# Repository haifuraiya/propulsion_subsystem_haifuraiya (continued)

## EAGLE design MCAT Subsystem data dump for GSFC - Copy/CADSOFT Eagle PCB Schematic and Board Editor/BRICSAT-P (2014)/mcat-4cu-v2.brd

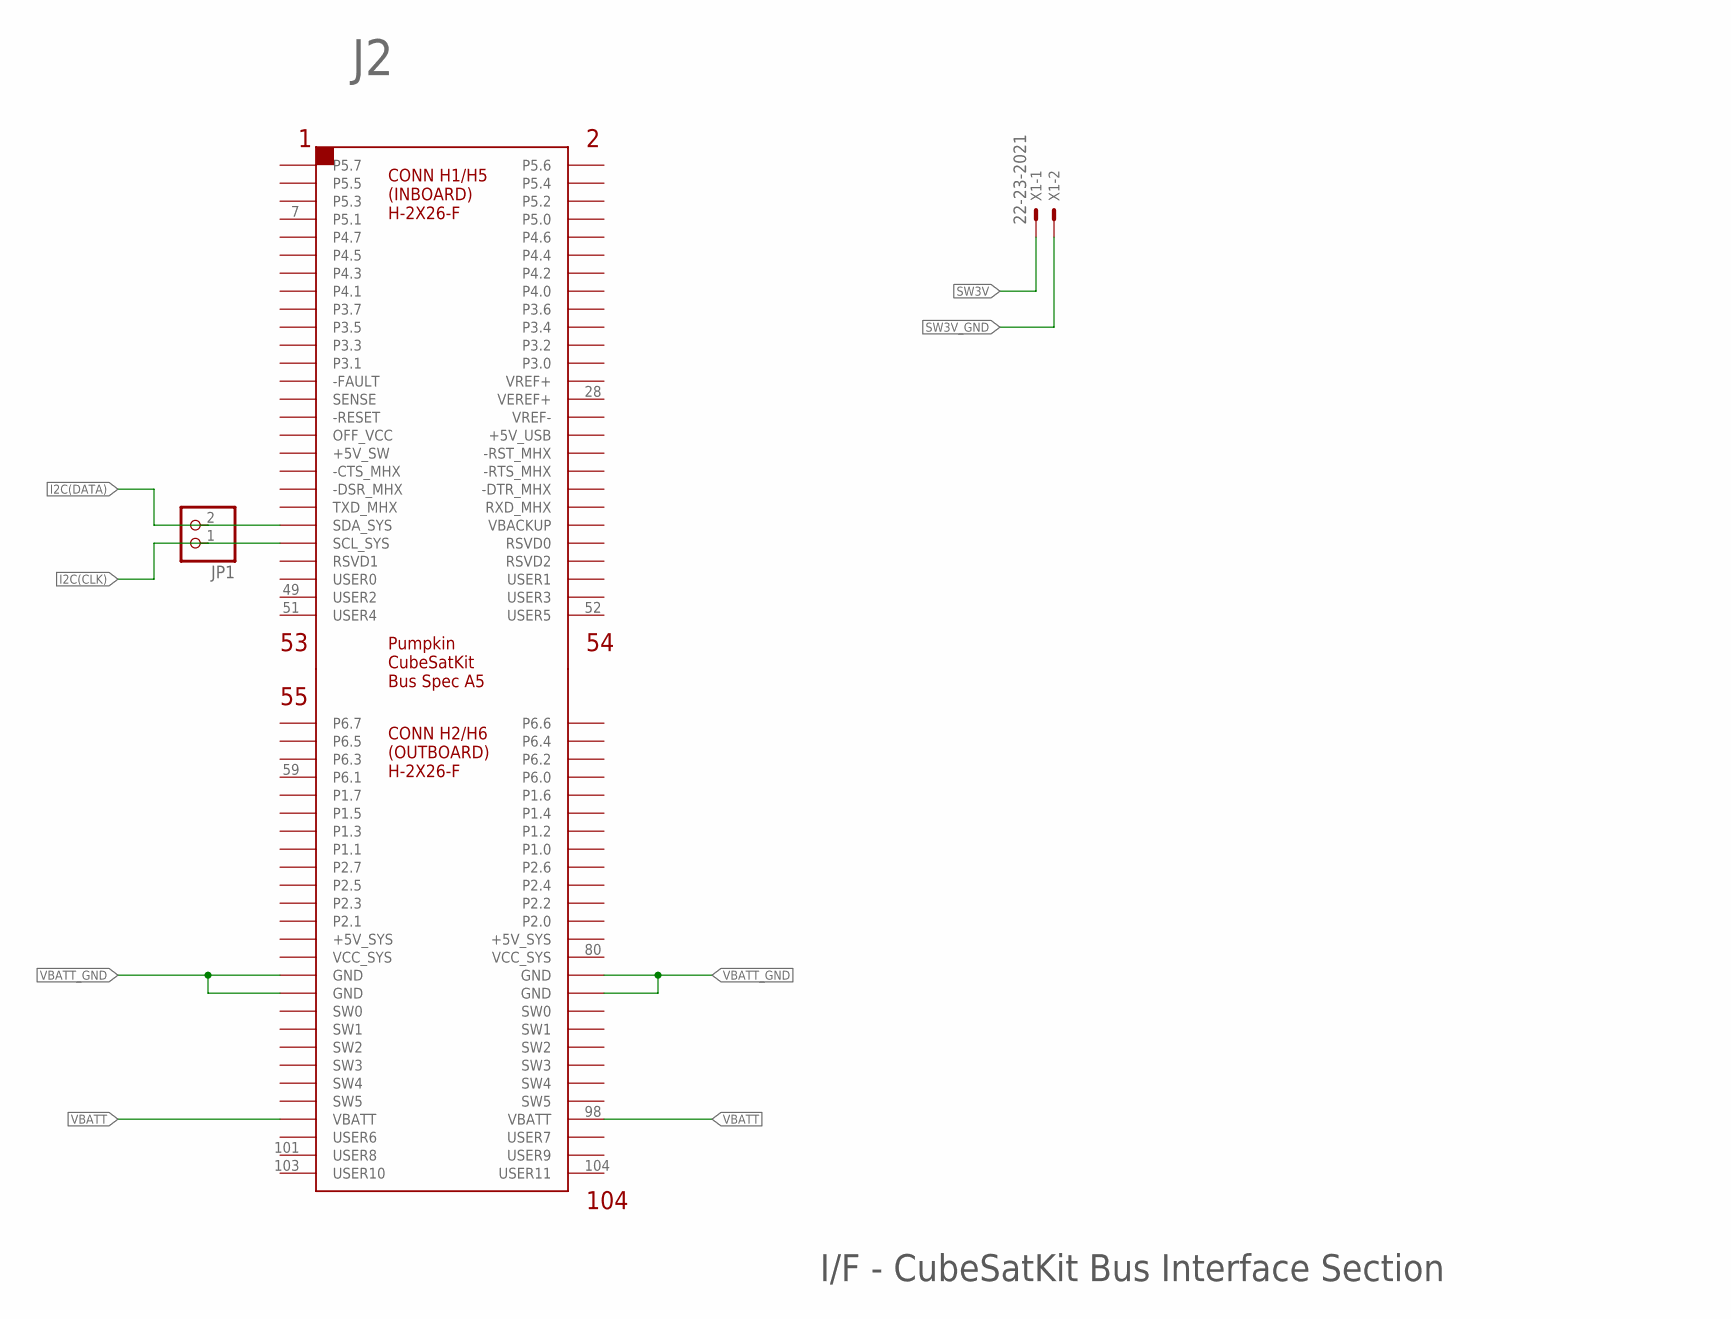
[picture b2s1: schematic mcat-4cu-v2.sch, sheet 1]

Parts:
J2: CSK-BUS-CONN2X2X26; CSK-BUS-PKG
JP1: PINHD-1X2; 1X02
X1: 22-23-2021

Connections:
I2C(CLK): J2.43 (SCL_SYS), JP1.1; also elsewhere on the board
I2C(DATA): J2.41 (SDA_SYS), JP1.2; also elsewhere on the board
unnamed: J2.82 (GND), J2.84 (GND)
SW3V: X1.1; also elsewhere on the board
SW3V_GND: X1.2; also elsewhere on the board
VBATT: J2.97 (VBATT), J2.98 (VBATT); also elsewhere on the board
VBATT_GND: J2.81 (GND), J2.83 (GND); also elsewhere on the board

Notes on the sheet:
I/F - CubeSatKit Bus Interface Section

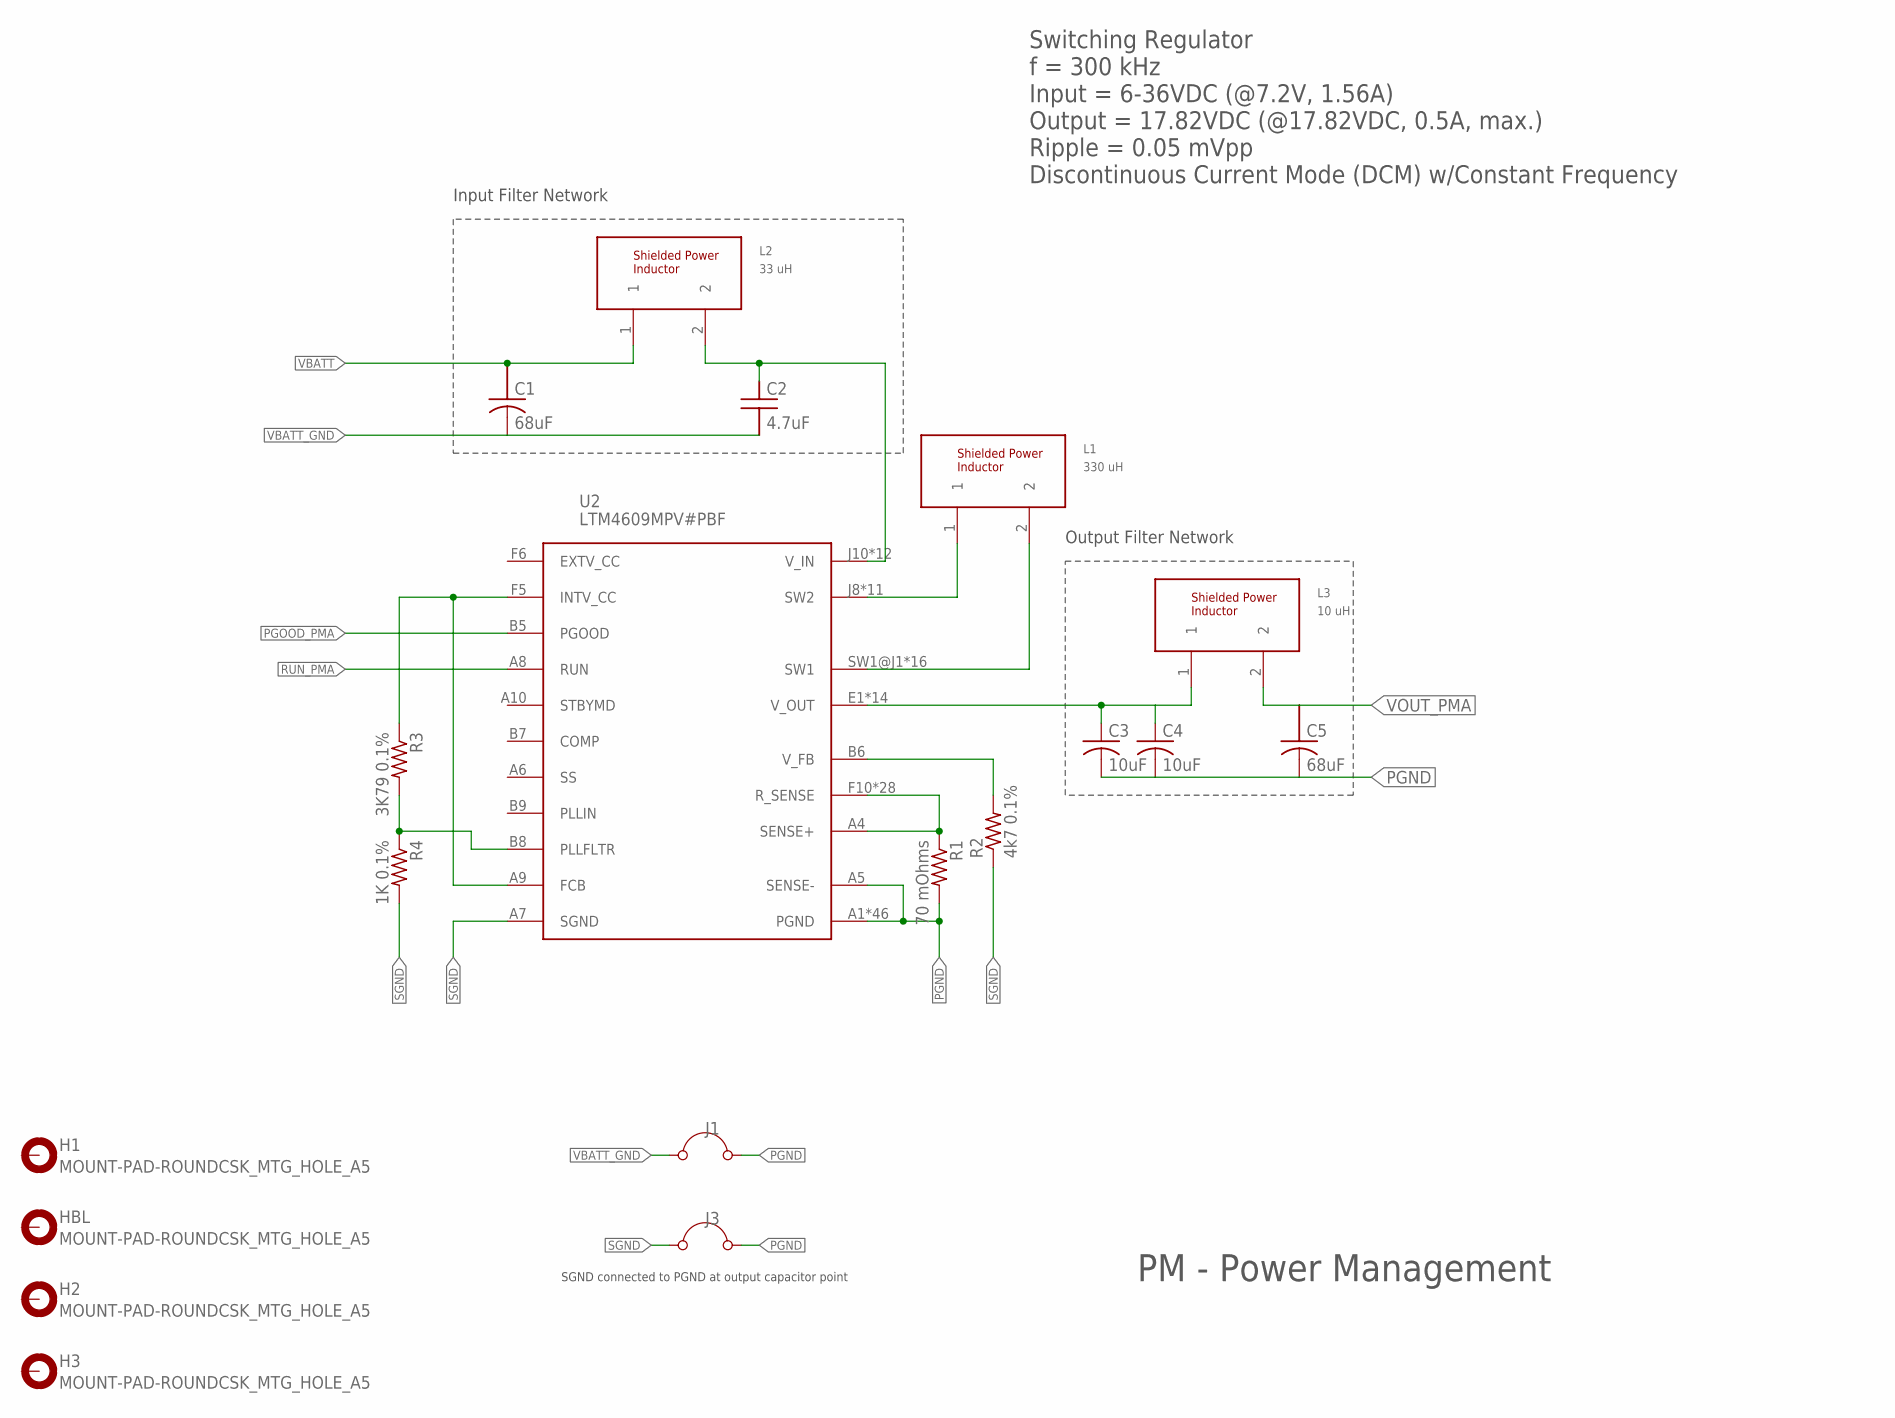
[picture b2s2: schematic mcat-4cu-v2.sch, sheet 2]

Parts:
C1, C5: 68uF; OS-CON-SVPF-F12
C2: 4.7uF; MLCC-X7R-1210
C3, C4: 10uF; C1210K
H1, H2, H3: MOUNT-PAD-ROUNDCSK_MTG_HOLE_A5; CSK_MOUNTING_HOLE
HBL: MOUNT-PAD-ROUNDCSK_MTG_HOLE_A5; CSK_MOUNTING_HOLE
J1, J3: JUMPER; 05
L1: 330 uH; MSS1048
L2: 33 uH; MSS1048
L3: 10 uH; SERIES-POWER-INDUCTORS
R1: 70 mOhms; R1206
R2: 4k7 0.1%; R0603
R3: 3K79 0.1%; R0805
R4: 1K 0.1%; R0805
U2: LTM4609MPV#PBF; LGA-141-LTC-05-08-1840-B

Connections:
INTVCC_OUT: R3.1, U2.A9 (FCB), U2.F5 (INTV_CC)
unnamed: R1.1, U2.A4 (SENSE+), U2.F10 (R_SENSE), U2.F11 (R_SENSE), U2.F12 (R_SENSE), U2.G5 (R_SENSE), U2.G6 (R_SENSE), U2.G7 (R_SENSE), U2.G8 (R_SENSE), U2.G9 (R_SENSE), U2.G10 (R_SENSE), U2.G11 (R_SENSE), U2.G12 (R_SENSE), U2.H5 (R_SENSE), U2.H6 (R_SENSE), U2.H7 (R_SENSE), U2.H8 (R_SENSE), U2.H9 (R_SENSE), U2.H10 (R_SENSE), U2.H11 (R_SENSE), U2.H12 (R_SENSE), U2.J5 (R_SENSE), U2.J6 (R_SENSE), U2.J7 (R_SENSE), U2.K5 (R_SENSE), U2.K6 (R_SENSE), U2.L5 (R_SENSE), U2.L6 (R_SENSE), U2.M5 (R_SENSE), U2.M6 (R_SENSE)
unnamed: R2.2, U2.B6 (V_FB)
PGND: C3.2, C4.2, C5.K1 (K), J1.2 (-), J3.2 (-), R1.2, U2.A1 (PGND), U2.A2 (PGND), U2.A3 (PGND), U2.A5 (SENSE-), U2.A11 (PGND), U2.A12 (PGND), U2.B1 (PGND), U2.B2 (PGND), U2.B3 (PGND), U2.B4 (PGND), U2.B10 (PGND), U2.B11 (PGND), U2.B12 (PGND), U2.C1 (PGND), U2.C2 (PGND), U2.C3 (PGND), U2.C4 (PGND), U2.C5 (PGND), U2.C6 (PGND), U2.C7 (PGND), U2.C8 (PGND), U2.C9 (PGND), U2.C10 (PGND), U2.C11 (PGND), U2.C12 (PGND), U2.D1 (PGND), U2.D2 (PGND), U2.D3 (PGND), U2.D4 (PGND), U2.D5 (PGND), U2.D6 (PGND), U2.D7 (PGND), U2.D8 (PGND), U2.D9 (PGND), U2.D10 (PGND), U2.D11 (PGND), U2.D12 (PGND), U2.E3 (PGND), U2.E4 (PGND), U2.E5 (PGND), U2.E6 (PGND), U2.E7 (PGND), U2.E8 (PGND), U2.E9 (PGND), U2.E10 (PGND), U2.E11 (PGND), U2.E12 (PGND)
PGOOD_PMA: U2.B5 (PGOOD)
RUN_PMA: U2.A8 (RUN)
SETFREQ: R3.2, R4.1, U2.B8 (PLLFLTR)
SGND: J3.1 (+), R2.1, R4.2, U2.A7 (SGND); also elsewhere on the board
SW1: L1.2, U2.SW1@J1 (SW1), U2.SW1@J2 (SW1), U2.SW1@J3 (SW1), U2.SW1@J4 (SW1), U2.SW1@K1 (SW1), U2.SW1@K2 (SW1), U2.SW1@K3 (SW1), U2.SW1@K4 (SW1), U2.SW1@L1 (SW1), U2.SW1@L2 (SW1), U2.SW1@L3 (SW1), U2.SW1@L4 (SW1), U2.SW1@M1 (SW1), U2.SW1@M2 (SW1), U2.SW1@M3 (SW1), U2.SW1@M4 (SW1)
SW2: L1.1, U2.J8 (SW2), U2.J9 (SW2), U2.K7 (SW2), U2.K8 (SW2), U2.K9 (SW2), U2.L7 (SW2), U2.L8 (SW2), U2.L9 (SW2), U2.M7 (SW2), U2.M8 (SW2), U2.M9 (SW2)
VBATT: C1.A1 (A), L2.1; also elsewhere on the board
VBATT_GND: C1.K1 (K), C2.2, J1.1 (+); also elsewhere on the board
VIN_PMA: C2.1, L2.2, U2.J10 (V_IN), U2.J11 (V_IN), U2.J12 (V_IN), U2.K10 (V_IN), U2.K11 (V_IN), U2.K12 (V_IN), U2.L10 (V_IN), U2.L11 (V_IN), U2.L12 (V_IN), U2.M10 (V_IN), U2.M11 (V_IN), U2.M12 (V_IN)
VOUTA: C3.1, C4.1, L3.1, U2.E1 (V_OUT), U2.E2 (V_OUT), U2.F1 (V_OUT), U2.F2 (V_OUT), U2.F3 (V_OUT), U2.F4 (V_OUT), U2.G1 (V_OUT), U2.G2 (V_OUT), U2.G3 (V_OUT), U2.G4 (V_OUT), U2.H2 (V_OUT), U2.H3 (V_OUT), U2.H4 (V_OUT), U2.VOUT (V_OUT)
VOUT_PMA: C5.A1 (A), L3.2

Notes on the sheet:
PM - Power Management
Input Filter Network
SGND connected to PGND at output capacitor point
Output Filter Network
Switching Regulator f = 300 kHz Input = 6-36VDC (@7.2V, 1.56A) Output = 17.82VDC (@17.82VDC, 0.5A, max.) Ripple = 0.05 mVpp Discontinuous Current Mode (DCM) w/Constant Frequency

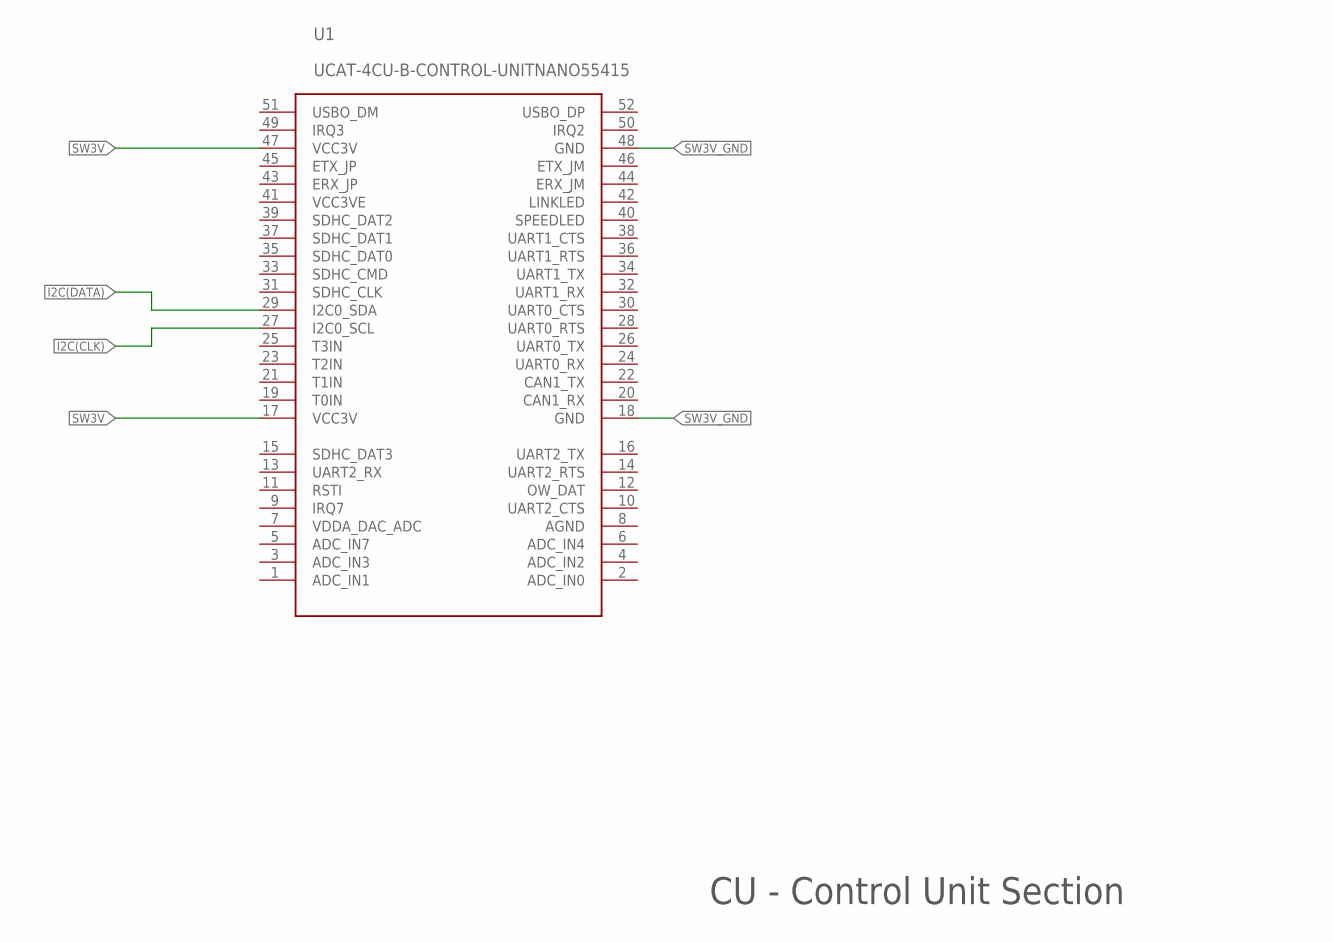
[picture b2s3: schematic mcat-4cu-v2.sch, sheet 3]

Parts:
U1: UCAT-4CU-B-CONTROL-UNITNANO55415; MOLEX-MINI-PCI-EXPRESS-8MM-52CKT

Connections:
I2C(CLK): U1.27 (I2C0_SCL); also elsewhere on the board
I2C(DATA): U1.29 (I2C0_SDA); also elsewhere on the board
SW3V: U1.17 (VCC3V), U1.47 (VCC3V); also elsewhere on the board
SW3V_GND: U1.48 (GND); also elsewhere on the board

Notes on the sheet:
CU - Control Unit Section

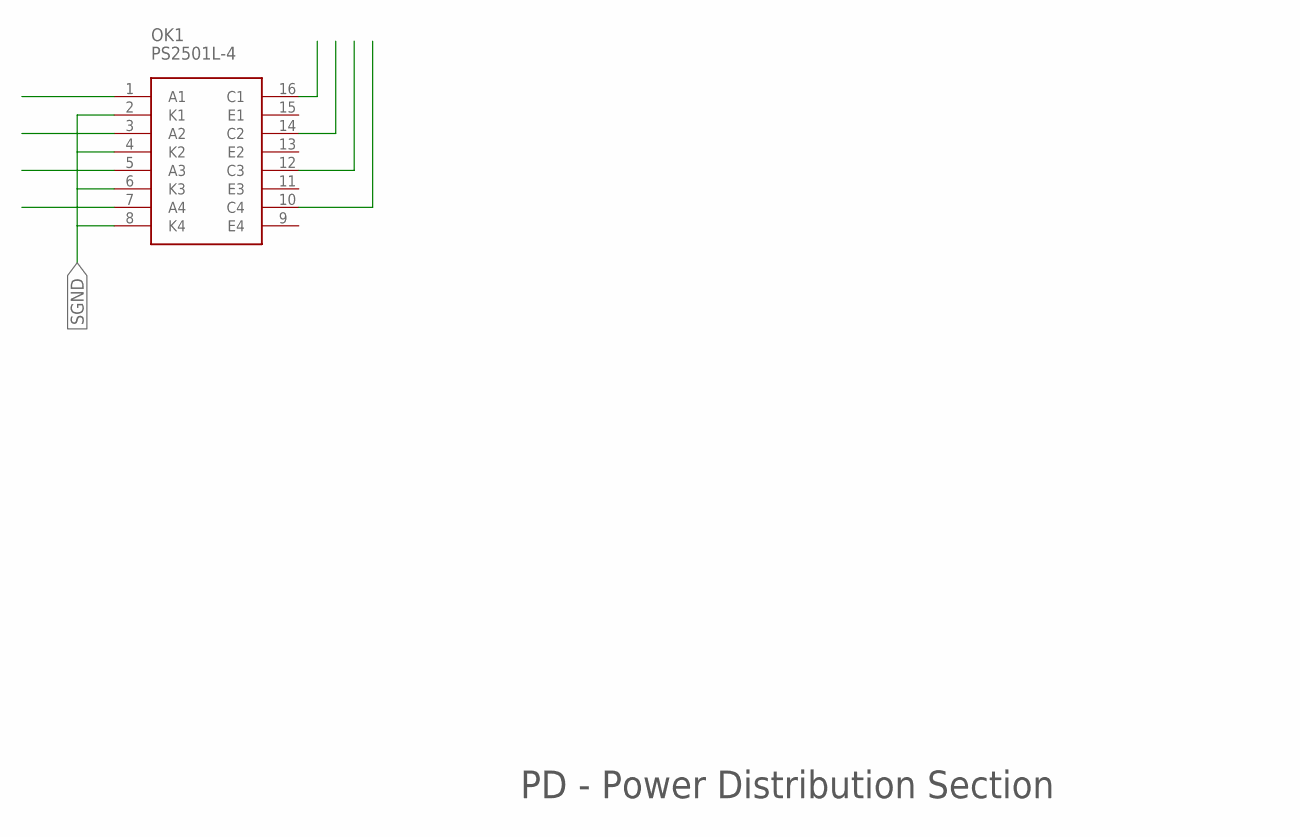
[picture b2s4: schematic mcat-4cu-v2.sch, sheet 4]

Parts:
OK1: PS2501L-4

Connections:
SGND: OK1.2 (K1), OK1.4 (K2), OK1.6 (K3), OK1.8 (K4); also elsewhere on the board

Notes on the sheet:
PD - Power Distribution Section

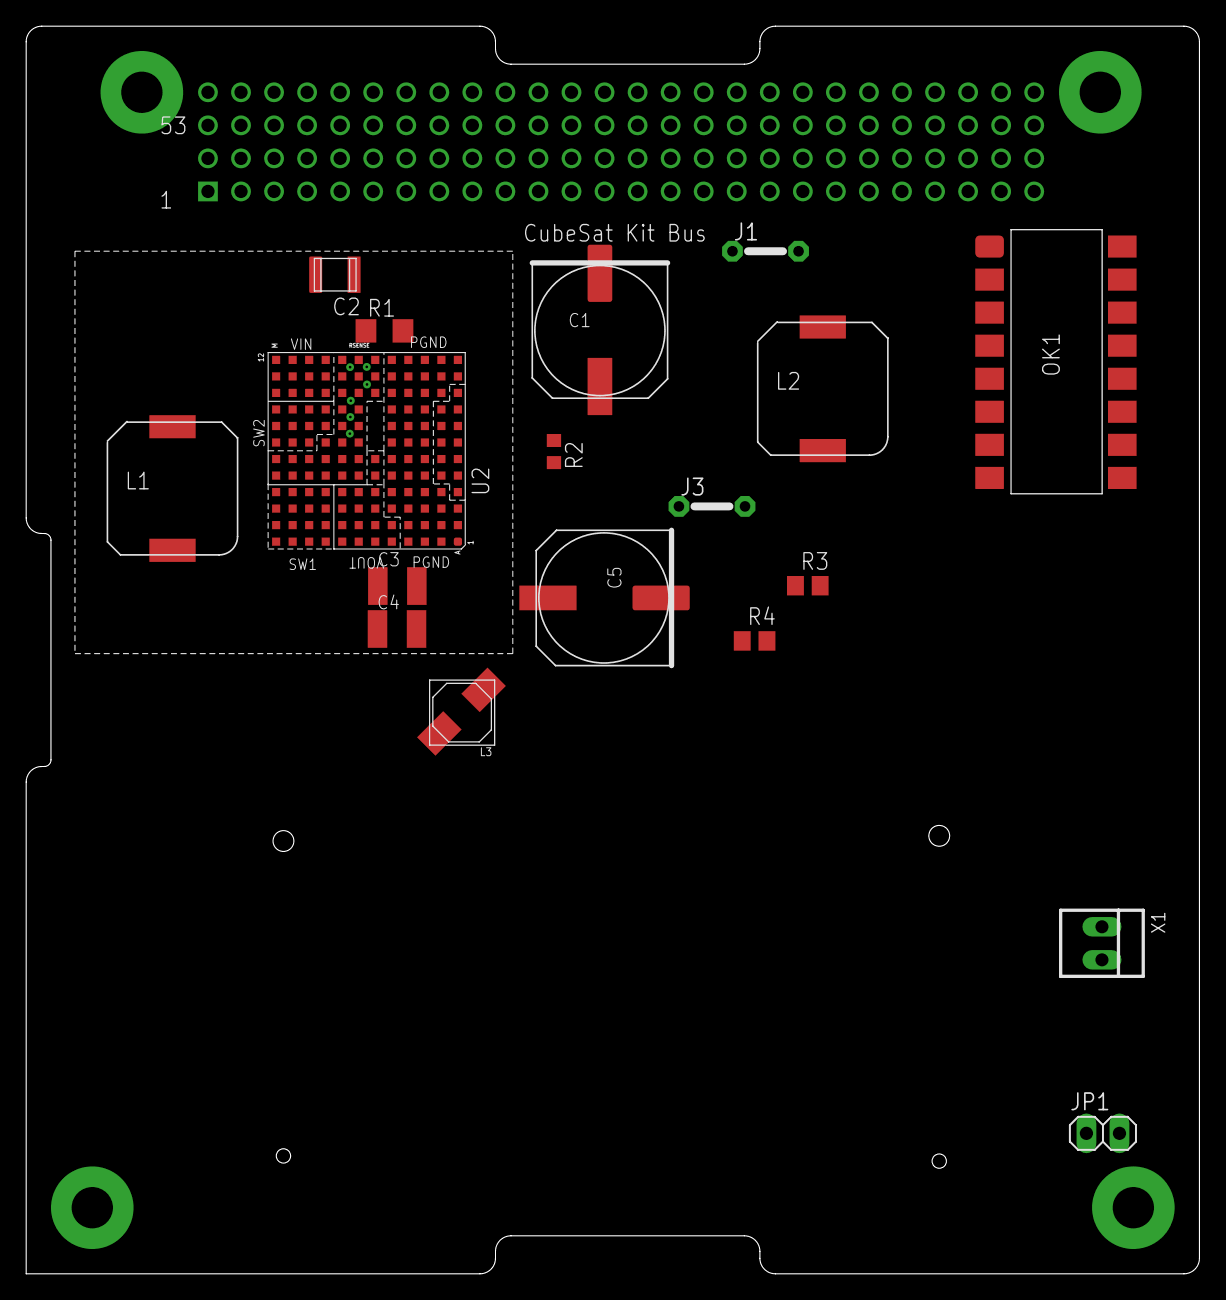
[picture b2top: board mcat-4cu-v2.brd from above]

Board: 4 copper layers, 90.2 x 95.9 mm, 24 parts (1 on the bottom side), 18 nets.

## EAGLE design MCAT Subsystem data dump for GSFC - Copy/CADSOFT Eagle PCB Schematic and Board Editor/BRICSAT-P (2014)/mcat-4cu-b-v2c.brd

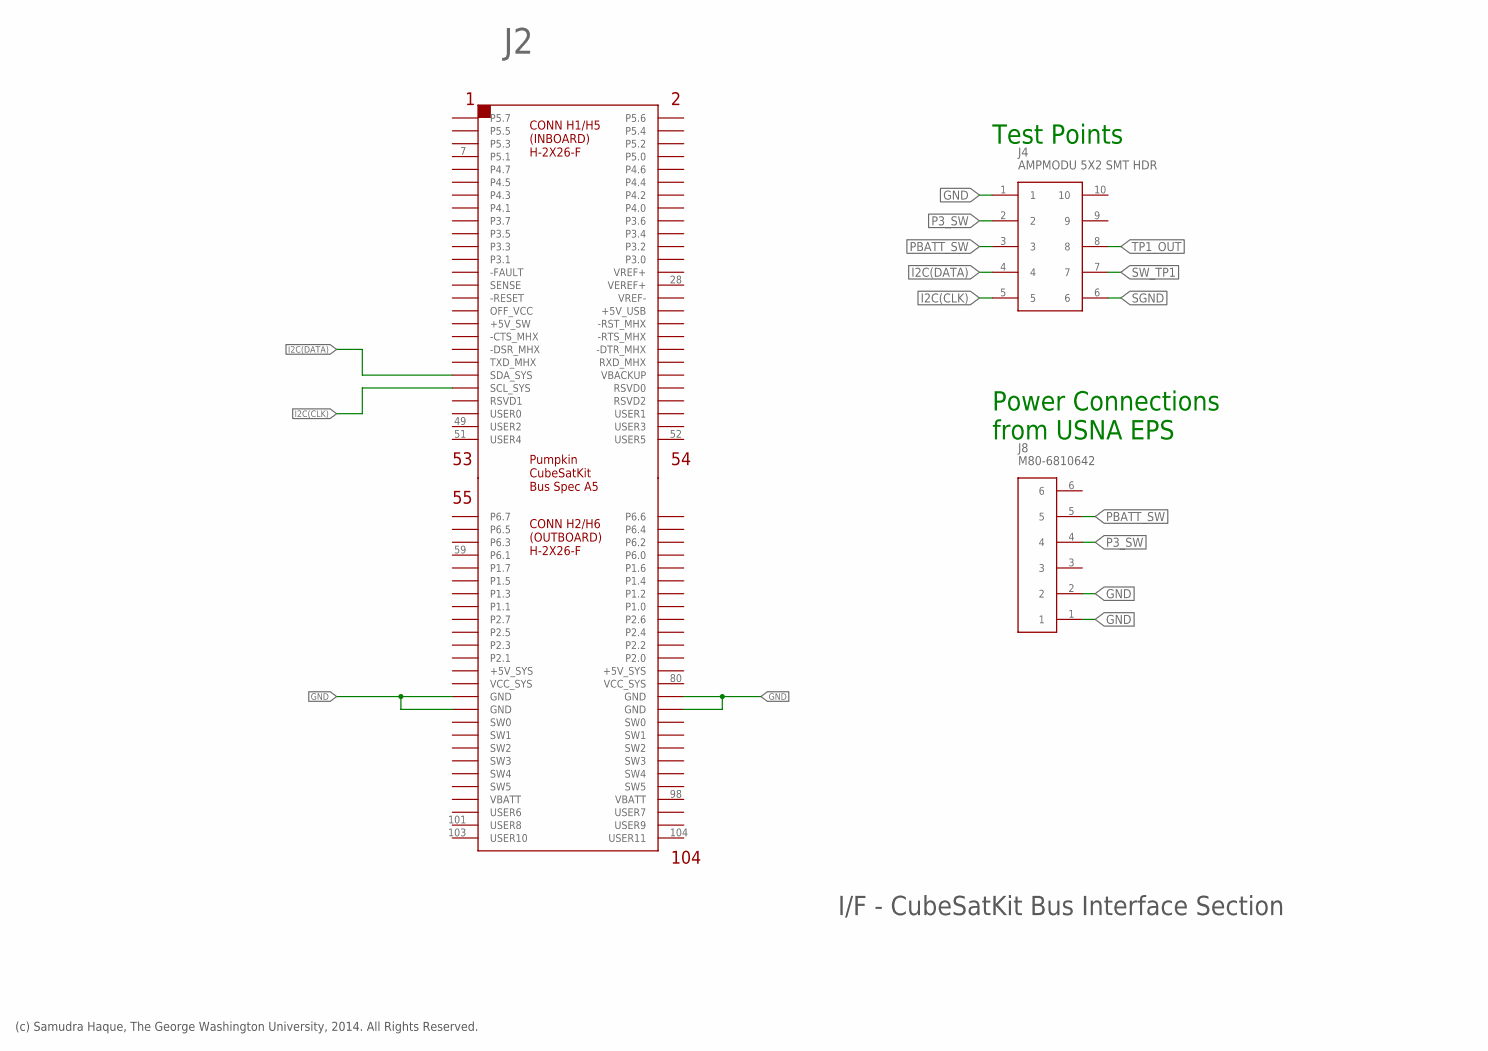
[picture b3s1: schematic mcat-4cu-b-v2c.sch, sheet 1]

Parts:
J2: CSK-BUS-CONN2X2X26; CSK-BUS-PKG
J4: AMPMODU 5X2 SMT HDR; AMPMODU-SMT-PIN-HEADER-5X2
J8: M80-6810642; M80-68106

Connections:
GND: J2.81 (GND), J2.82 (GND), J2.83 (GND), J2.84 (GND), J4.1, J8.1, J8.2; also elsewhere on the board
I2C(CLK): J2.43 (SCL_SYS), J4.5; also elsewhere on the board
I2C(DATA): J2.41 (SDA_SYS), J4.4; also elsewhere on the board
P3_SW: J4.2, J8.4; also elsewhere on the board
PBATT_SW: J4.3, J8.5; also elsewhere on the board
SGND: J4.6; also elsewhere on the board
SW_TP1: J4.7; also elsewhere on the board
TP1_OUT: J4.8; also elsewhere on the board

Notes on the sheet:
I/F - CubeSatKit Bus Interface Section
Test Points
(c) Samudra Haque, The George Washington University, 2014. All Rights Reserved.
Power Connections from USNA EPS

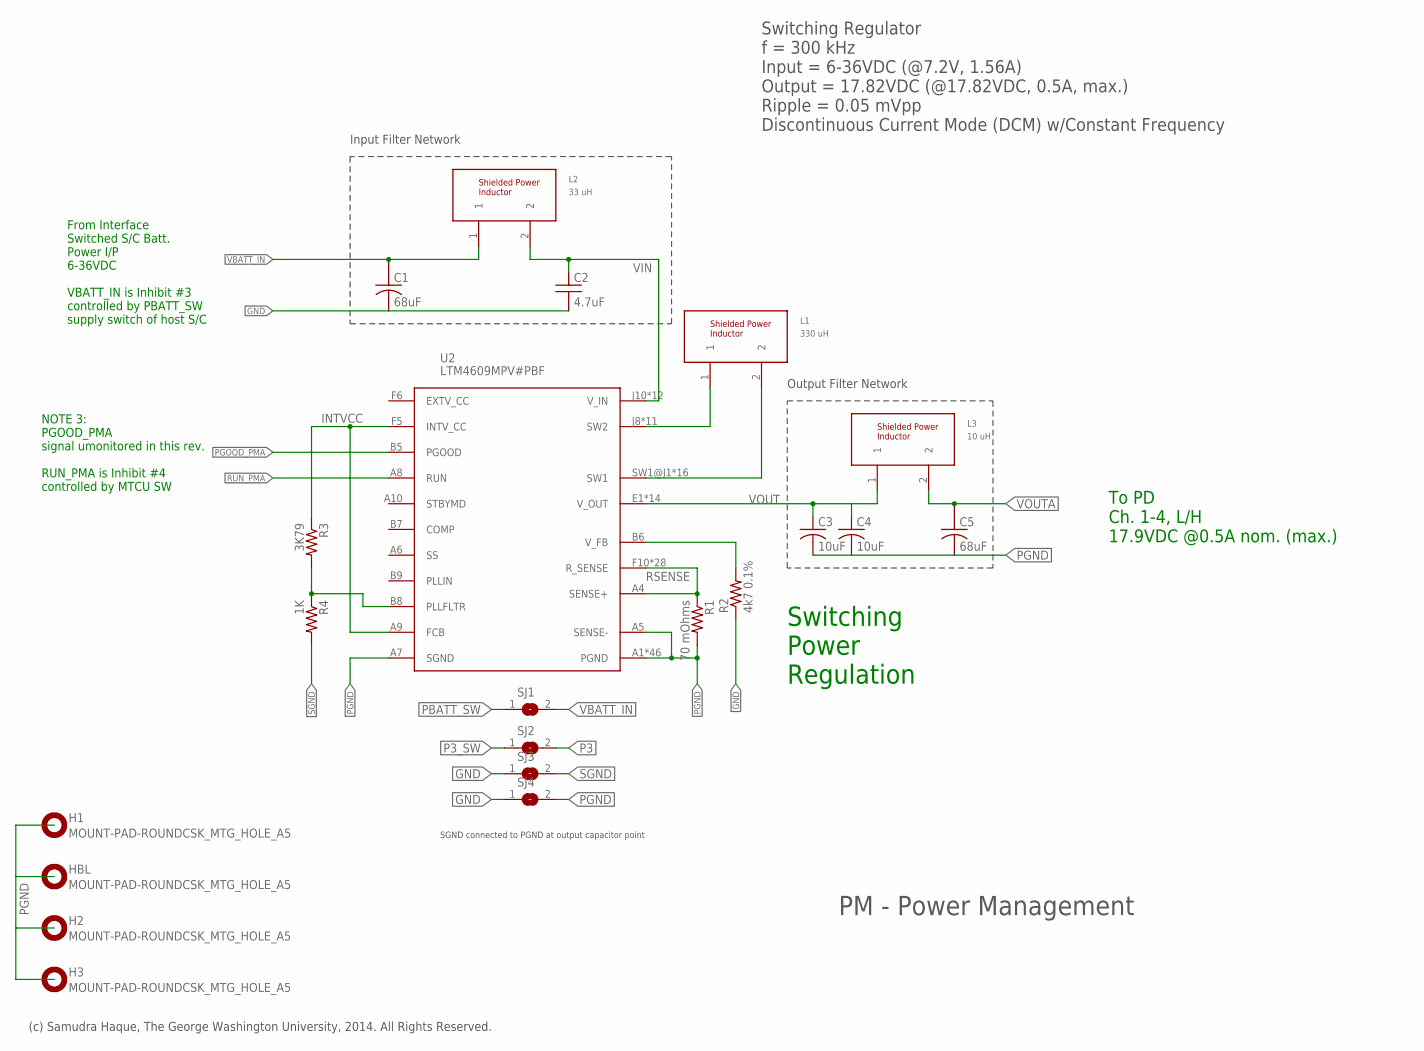
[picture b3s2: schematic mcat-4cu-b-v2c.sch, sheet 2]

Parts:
C1, C5: 68uF; OS-CON-SVPF-F12
C2: 4.7uF; MLCC-X7R-1210
C3, C4: 10uF; C1210K
H1, H2, H3: MOUNT-PAD-ROUNDCSK_MTG_HOLE_A5; CSK_MOUNTING_HOLE
HBL: MOUNT-PAD-ROUNDCSK_MTG_HOLE_A5; CSK_MOUNTING_HOLE
L1: 330 uH; MSS1048
L2: 33 uH; MSS1048
L3: 10 uH; SERIES-POWER-INDUCTORS
R1: 70 mOhms; R1206
R2: 4k7 0.1%; R0603
R3: 3K79; R0805
R4: 1K; R0805
SJ1, SJ2, SJ3, SJ4: SJ
U2: LTM4609MPV#PBF; LGA-141-LTC-05-08-1840-B

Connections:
GND: C1.K1 (K), C2.2, R2.1, SJ3.1, SJ4.1; also elsewhere on the board
INTVCC: R3.1, U2.A9 (FCB), U2.F5 (INTV_CC); also elsewhere on the board
unnamed: R2.2, U2.B6 (V_FB)
P3: SJ2.2; also elsewhere on the board
P3_SW: SJ2.1; also elsewhere on the board
PBATT_SW: SJ1.1; also elsewhere on the board
PGND: C3.2, C4.2, C5.K1 (K), H1.P$1, H2.P$1, H3.P$1, HBL.P$1, R1.2, SJ4.2, U2.A1 (PGND), U2.A2 (PGND), U2.A3 (PGND), U2.A5 (SENSE-), U2.A7 (SGND), U2.A11 (PGND), U2.A12 (PGND), U2.B1 (PGND), U2.B2 (PGND), U2.B3 (PGND), U2.B4 (PGND), U2.B10 (PGND), U2.B11 (PGND), U2.B12 (PGND), U2.C1 (PGND), U2.C2 (PGND), U2.C3 (PGND), U2.C4 (PGND), U2.C5 (PGND), U2.C6 (PGND), U2.C7 (PGND), U2.C8 (PGND), U2.C9 (PGND), U2.C10 (PGND), U2.C11 (PGND), U2.C12 (PGND), U2.D1 (PGND), U2.D2 (PGND), U2.D3 (PGND), U2.D4 (PGND), U2.D5 (PGND), U2.D6 (PGND), U2.D7 (PGND), U2.D8 (PGND), U2.D9 (PGND), U2.D10 (PGND), U2.D11 (PGND), U2.D12 (PGND), U2.E3 (PGND), U2.E4 (PGND), U2.E5 (PGND), U2.E6 (PGND), U2.E7 (PGND), U2.E8 (PGND), U2.E9 (PGND), U2.E10 (PGND), U2.E11 (PGND), U2.E12 (PGND); also elsewhere on the board
PGOOD_PMA: U2.B5 (PGOOD)
RSENSE: R1.1, U2.A4 (SENSE+), U2.F10 (R_SENSE), U2.F11 (R_SENSE), U2.F12 (R_SENSE), U2.G5 (R_SENSE), U2.G6 (R_SENSE), U2.G7 (R_SENSE), U2.G8 (R_SENSE), U2.G9 (R_SENSE), U2.G10 (R_SENSE), U2.G11 (R_SENSE), U2.G12 (R_SENSE), U2.H5 (R_SENSE), U2.H6 (R_SENSE), U2.H7 (R_SENSE), U2.H8 (R_SENSE), U2.H9 (R_SENSE), U2.H10 (R_SENSE), U2.H11 (R_SENSE), U2.H12 (R_SENSE), U2.J5 (R_SENSE), U2.J6 (R_SENSE), U2.J7 (R_SENSE), U2.K5 (R_SENSE), U2.K6 (R_SENSE), U2.L5 (R_SENSE), U2.L6 (R_SENSE), U2.M5 (R_SENSE), U2.M6 (R_SENSE)
RUN_PMA: U2.A8 (RUN)
SETFREQ: R3.2, R4.1, U2.B8 (PLLFLTR)
SGND: R4.2, SJ3.2; also elsewhere on the board
SW1: L1.2, U2.SW1@J1 (SW1), U2.SW1@J2 (SW1), U2.SW1@J3 (SW1), U2.SW1@J4 (SW1), U2.SW1@K1 (SW1), U2.SW1@K2 (SW1), U2.SW1@K3 (SW1), U2.SW1@K4 (SW1), U2.SW1@L1 (SW1), U2.SW1@L2 (SW1), U2.SW1@L3 (SW1), U2.SW1@L4 (SW1), U2.SW1@M1 (SW1), U2.SW1@M2 (SW1), U2.SW1@M3 (SW1), U2.SW1@M4 (SW1)
SW2: L1.1, U2.J8 (SW2), U2.J9 (SW2), U2.K7 (SW2), U2.K8 (SW2), U2.K9 (SW2), U2.L7 (SW2), U2.L8 (SW2), U2.L9 (SW2), U2.M7 (SW2), U2.M8 (SW2), U2.M9 (SW2)
VBATT_IN: C1.A1 (A), L2.1, SJ1.2
VIN: C2.1, L2.2, U2.J10 (V_IN), U2.J11 (V_IN), U2.J12 (V_IN), U2.K10 (V_IN), U2.K11 (V_IN), U2.K12 (V_IN), U2.L10 (V_IN), U2.L11 (V_IN), U2.L12 (V_IN), U2.M10 (V_IN), U2.M11 (V_IN), U2.M12 (V_IN)
VOUT: C3.1, C4.1, L3.1, U2.E1 (V_OUT), U2.E2 (V_OUT), U2.F1 (V_OUT), U2.F2 (V_OUT), U2.F3 (V_OUT), U2.F4 (V_OUT), U2.G1 (V_OUT), U2.G2 (V_OUT), U2.G3 (V_OUT), U2.G4 (V_OUT), U2.H2 (V_OUT), U2.H3 (V_OUT), U2.H4 (V_OUT), U2.VOUT (V_OUT)
VOUTA: C5.A1 (A), L3.2; also elsewhere on the board

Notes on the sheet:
PM - Power Management
Input Filter Network
SGND connected to PGND at output capacitor point
Output Filter Network
Switching Regulator f = 300 kHz Input = 6-36VDC (@7.2V, 1.56A) Output = 17.82VDC (@17.82VDC, 0.5A, max.) Ripple = 0.05 mVpp Discontinuous Current Mode (DCM) w/Constant Frequency
(c) Samudra Haque, The George Washington University, 2014. All Rights Reserved.
NOTE 3: PGOOD_PMA signal umonitored in this rev. RUN_PMA is Inhibit #4 controlled by MTCU SW
Switching Power Regulation
To PD Ch. 1-4, L/H 17.9VDC @0.5A nom. (max.)
From Interface Switched S/C Batt. Power I/P 6-36VDC VBATT_IN is Inhibit #3 controlled by PBATT_SW supply switch of host S/C

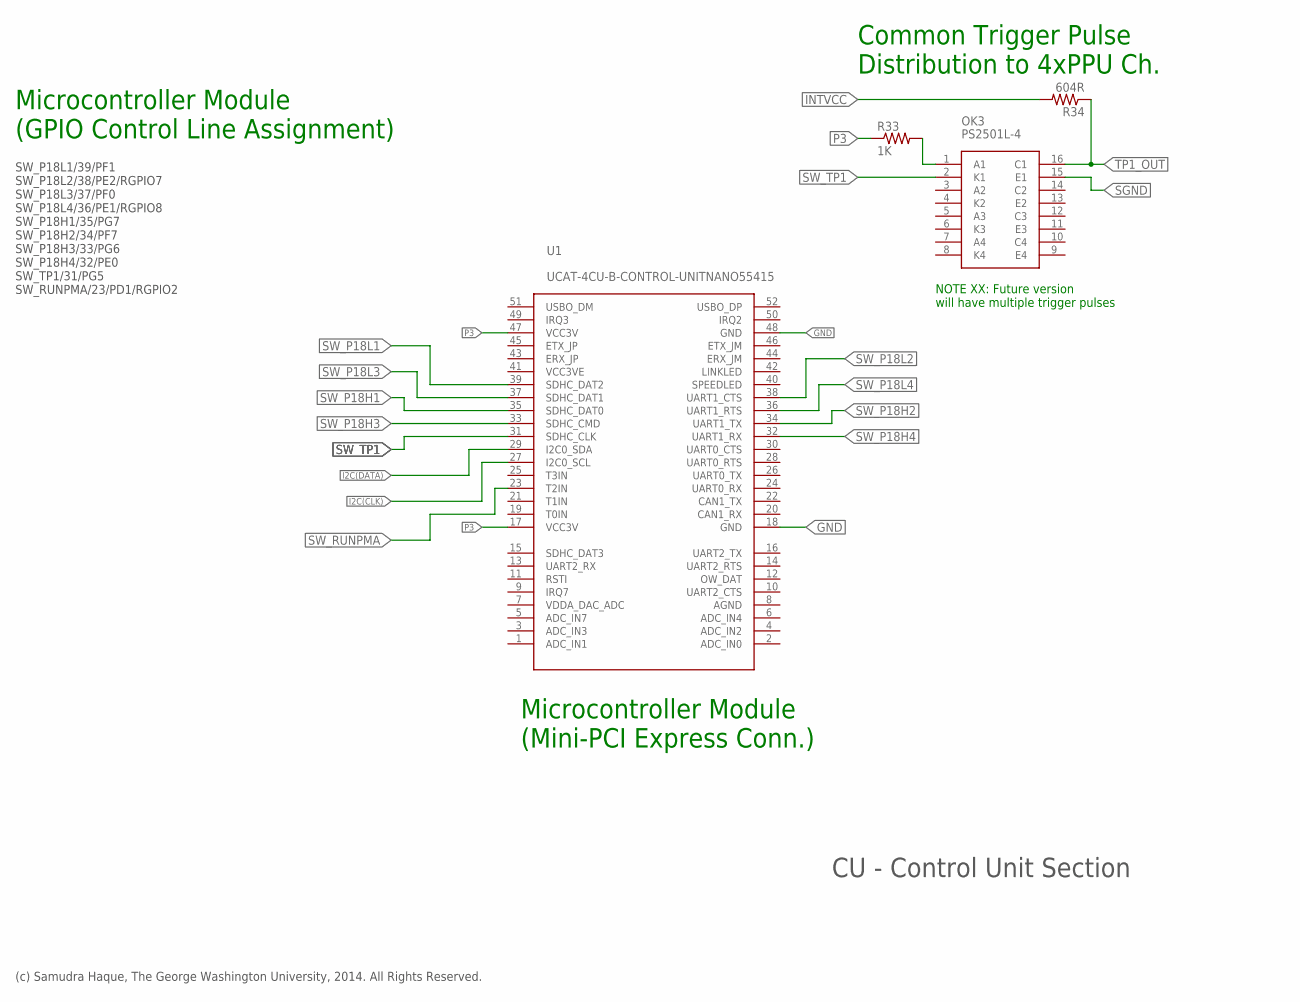
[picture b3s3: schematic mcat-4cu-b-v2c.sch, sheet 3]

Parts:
OK3: PS2501L-4
R33: 1K; R0805
R34: 604R; R0805
U1: UCAT-4CU-B-CONTROL-UNITNANO55415; MOLEX-MINI-PCI-EXPRESS-8MM-52CKT

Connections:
GND: U1.18 (GND), U1.48 (GND); also elsewhere on the board
I2C(CLK): U1.27 (I2C0_SCL); also elsewhere on the board
I2C(DATA): U1.29 (I2C0_SDA); also elsewhere on the board
INTVCC: R34.2; also elsewhere on the board
unnamed: OK3.1 (A1), R33.2
P3: R33.1, U1.17 (VCC3V), U1.47 (VCC3V); also elsewhere on the board
SGND: OK3.15 (E1); also elsewhere on the board
SW_P18H1: U1.35 (SDHC_DAT0); also elsewhere on the board
SW_P18H2: U1.34 (UART1_TX); also elsewhere on the board
SW_P18H3: U1.33 (SDHC_CMD); also elsewhere on the board
SW_P18H4: U1.32 (UART1_RX); also elsewhere on the board
SW_P18L1: U1.39 (SDHC_DAT2); also elsewhere on the board
SW_P18L2: U1.38 (UART1_CTS); also elsewhere on the board
SW_P18L3: U1.37 (SDHC_DAT1); also elsewhere on the board
SW_P18L4: U1.36 (UART1_RTS); also elsewhere on the board
SW_RUNPMA: U1.23 (T2IN)
SW_TP1: OK3.2 (K1), U1.31 (SDHC_CLK); also elsewhere on the board
TP1_OUT: OK3.16 (C1), R34.1; also elsewhere on the board

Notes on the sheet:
CU - Control Unit Section
SW_P18L1/39/PF1 SW_P18L2/38/PE2/RGPIO7 SW_P18L3/37/PF0 SW_P18L4/36/PE1/RGPIO8 SW_P18H1/35/PG7 SW_P18H2/34/PF7 SW_P18H3/33/PG6 SW_P18H4/32/PE0 SW_TP1/31/PG5 SW_RUNPMA/23/PD1/RGPIO2
(c) Samudra Haque, The George Washington University, 2014. All Rights Reserved.
Microcontroller Module (Mini-PCI Express Conn.)
Common Trigger Pulse Distribution to 4xPPU Ch.
NOTE XX: Future version will have multiple trigger pulses
Microcontroller Module (GPIO Control Line Assignment)

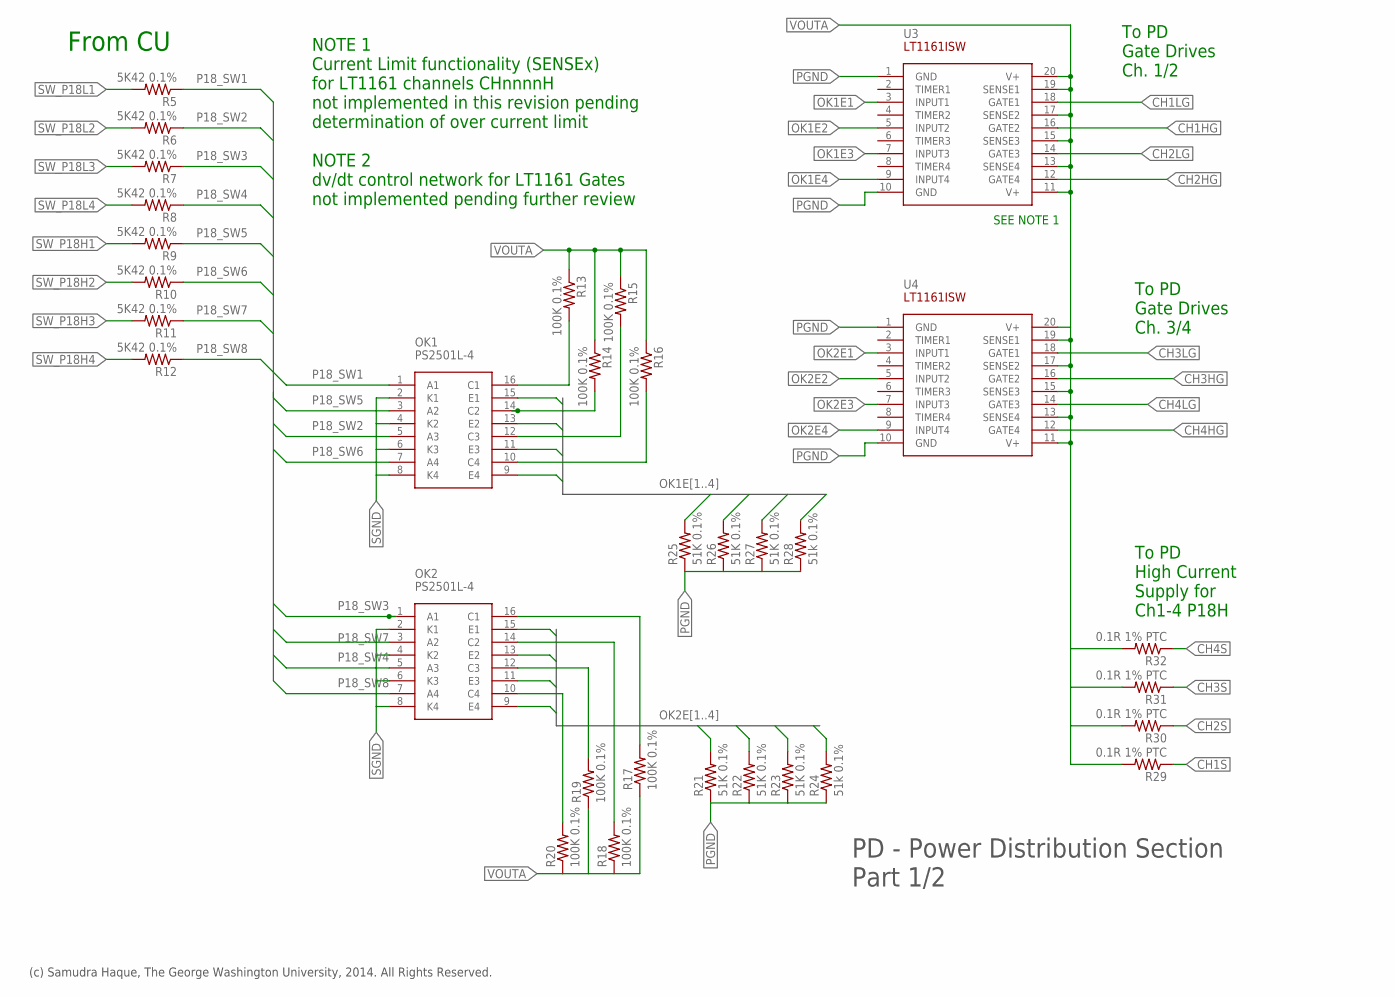
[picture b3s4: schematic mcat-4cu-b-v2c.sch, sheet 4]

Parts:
OK1, OK2: PS2501L-4
R5, R6, R7, R8, R9, R10, R11, R12: 5K42 0.1%; R1206
R13, R14, R15, R16, R17, R18, R19, R20: 100K 0.1%; R0402
R21, R22, R23, R25, R26, R27: 51K 0.1%; R0603
R24, R28: 51k 0.1%; R0603
R29, R30, R31, R32: 0.1R 1% PTC; R0402
U3, U4: LT1161ISW; 20-LEAD-PLASTIC-SO

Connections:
CH1HG: U3.16 (GATE2); also elsewhere on the board
CH1LG: U3.18 (GATE1); also elsewhere on the board
CH1S: R29.1; also elsewhere on the board
CH2HG: U3.12 (GATE4); also elsewhere on the board
CH2LG: U3.14 (GATE3); also elsewhere on the board
CH2S: R30.1; also elsewhere on the board
CH3HG: U4.16 (GATE2); also elsewhere on the board
CH3LG: U4.18 (GATE1); also elsewhere on the board
CH3S: R31.1; also elsewhere on the board
CH4HG: U4.12 (GATE4); also elsewhere on the board
CH4LG: U4.14 (GATE3); also elsewhere on the board
CH4S: R32.1; also elsewhere on the board
unnamed: OK1.16 (C1), R13.2
unnamed: OK1.14 (C2), R14.2
unnamed: OK1.12 (C3), R15.2
unnamed: OK1.10 (C4), R16.2
unnamed: OK2.16 (C1), R17.2
unnamed: OK2.14 (C2), R18.2
unnamed: OK2.12 (C3), R19.2
unnamed: OK2.10 (C4), R20.2
OK1E1: OK1.15 (E1), R25.2, U3.3 (INPUT1)
OK1E2: OK1.13 (E2), R26.2, U3.5 (INPUT2)
OK1E3: OK1.11 (E3), R27.2, U3.7 (INPUT3)
OK1E4: OK1.9 (E4), R28.2, U3.9 (INPUT4)
OK2E1: OK2.15 (E1), R21.2, U4.3 (INPUT1)
OK2E2: OK2.13 (E2), R22.2, U4.5 (INPUT2)
OK2E3: OK2.11 (E3), R23.2, U4.7 (INPUT3)
OK2E4: OK2.9 (E4), R24.2, U4.9 (INPUT4)
P18_SW1: OK1.1 (A1), R5.1
P18_SW2: OK1.5 (A3), R6.1
P18_SW3: OK2.1 (A1), R7.1
P18_SW4: OK2.5 (A3), R8.1
P18_SW5: OK1.3 (A2), R9.1
P18_SW6: OK1.7 (A4), R10.1
P18_SW7: OK2.3 (A2), R11.1
P18_SW8: OK2.7 (A4), R12.1
PGND: R21.1, R22.1, R23.1, R24.1, R25.1, R26.1, R27.1, R28.1, U3.1 (GND), U3.10 (GND), U4.1 (GND), U4.10 (GND); also elsewhere on the board
SGND: OK1.2 (K1), OK1.4 (K2), OK1.6 (K3), OK1.8 (K4), OK2.2 (K1), OK2.4 (K2), OK2.6 (K3), OK2.8 (K4); also elsewhere on the board
SW_P18H1: R9.2; also elsewhere on the board
SW_P18H2: R10.2; also elsewhere on the board
SW_P18H3: R11.2; also elsewhere on the board
SW_P18H4: R12.2; also elsewhere on the board
SW_P18L1: R5.2; also elsewhere on the board
SW_P18L2: R6.2; also elsewhere on the board
SW_P18L3: R7.2; also elsewhere on the board
SW_P18L4: R8.2; also elsewhere on the board
VOUTA: R13.1, R14.1, R15.1, R16.1, R17.1, R18.1, R19.1, R20.1, R29.2, R30.2, R31.2, R32.2, U3.11 (V+), U3.13 (SENSE4), U3.15 (SENSE3), U3.17 (SENSE2), U3.19 (SENSE1), U3.20 (V+), U4.11 (V+), U4.13 (SENSE4), U4.15 (SENSE3), U4.17 (SENSE2), U4.19 (SENSE1), U4.20 (V+); also elsewhere on the board

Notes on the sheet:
PD - Power Distribution Section Part 1/2
NOTE 1 Current Limit functionality (SENSEx) for LT1161 channels CHnnnnH not implemented in this revision pending determination of over current limit NOTE 2 dv/dt control network for LT1161 Gates not implemented pending further review
SEE NOTE 1
(c) Samudra Haque, The George Washington University, 2014. All Rights Reserved.
From CU
To PD Gate Drives Ch. 1/2
To PD High Current Supply for Ch1-4 P18H
To PD Gate Drives Ch. 3/4
